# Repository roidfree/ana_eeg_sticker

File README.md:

# ANA - EEG Focus Monitor

A Flutter app that connects to state-of-the-art biosignal patch via Bluetooth to monitor focus, stress, and mental state in real-time.

## 🧠 What is ANA?

ANA is a wireless EEG monitoring system that turns brain activity into actionable insights. Think of it as a fitness tracker for your mind - it measures focus levels, stress, and mental fatigue to help you optimize your cognitive performance.

## 📱 Features

- **Real-time EEG monitoring** via Bluetooth Low Energy
- **Live focus tracking** with visual feedback
- **Stress level detection** using brain wave analysis
- **Session recording** and playback
- **Clean, intuitive interface** designed for daily use

## 🚀 Quick Start

### Prerequisites
- Flutter SDK (3.16+)
- Android Studio or Xcode
- Compatible EEG device (OpenBCI Cyton, nRF52832 prototype)

### Installation
```bash
# Clone the repository
git clone https://github.com/your-username/ana-app.git
cd ana_eeg_sticker

# Install dependencies
flutter pub get

# Run the app
flutter run
```

## 📦 Dependencies

```yaml
dependencies:
  flutter_blue_plus: ^1.12.0  # BLE connectivity
  fl_chart: ^0.65.0           # Real-time charts
  riverpod: ^2.4.0            # State management
  hive: ^2.2.3                # Local storage
```

## 🔧 Usage

1. **Connect Device**: Turn on your EEG device and tap "Scan" in the app
2. **Start Session**: Once connected, press "Start Monitoring" 
3. **View Live Data**: Watch your brain waves and focus metrics in real-time
4. **Review Sessions**: Check your focus patterns and improvements over time

## 📊 How It Works

```
EEG Sensor → Bluetooth → Signal Processing → Algorithms (e.g Focus) → Live Display
```

The app does things like: filter EEG signals (1-40 Hz), extracts alpha and beta wave features, and calculates a real-time focus score based on established neuroscience research.

## 🧪 Signal Processing

- **Bandpass filtering**: Removes noise and isolates brain waves
- **Feature extraction**: Alpha (8-12 Hz) and Beta (13-30 Hz) power
- **Focus metric**: Alpha/Beta ratio with smoothing algorithm
- **Real-time processing**: <100ms latency for immediate feedback

## 🛠️ Development

### Project Structure
```
lib/
├── main.dart              # App entry point
├── models/                # Data structures
├── services/              # BLE and signal processing
├── screens/               # UI screens
└── widgets/               # Reusable components
```

### Running Tests
```bash
flutter test
```

### Building for Release
```bash
# Android
flutter build apk --release

# iOS
flutter build ios --release
```

## 📱 Screenshots

[Add screenshots of your app here]

## 🎯 Roadmap

- [x] BLE connectivity
- [x] Real-time EEG display
- [x] Basic focus metrics
- [ ] Advanced signal processing
- [ ] Cloud data sync
- [ ] Multi-device support
- [ ] Meditation guidance

## 🤝 Contributing

We're a small team building this in the open. Feel free to:
- Report bugs via GitHub Issues
- Suggest features
- Submit pull requests

## 📄 License

MIT License - see [LICENSE](LICENSE) file for details.

## 🔗 Hardware Compatibility

**Tested Devices:**
- OpenBCI Cyton Board
- Custom nRF52832 prototype

**BLE Requirements:**
- Bluetooth 4.0+
- Custom EEG data characteristic
- Sampling rate: 250+ Hz

## 📧 Contact

For questions about the project or collaboration opportunities, create an issue or reach out via GitHub.

---

**Built with ❤️ for better brain health and cognitive performance.**

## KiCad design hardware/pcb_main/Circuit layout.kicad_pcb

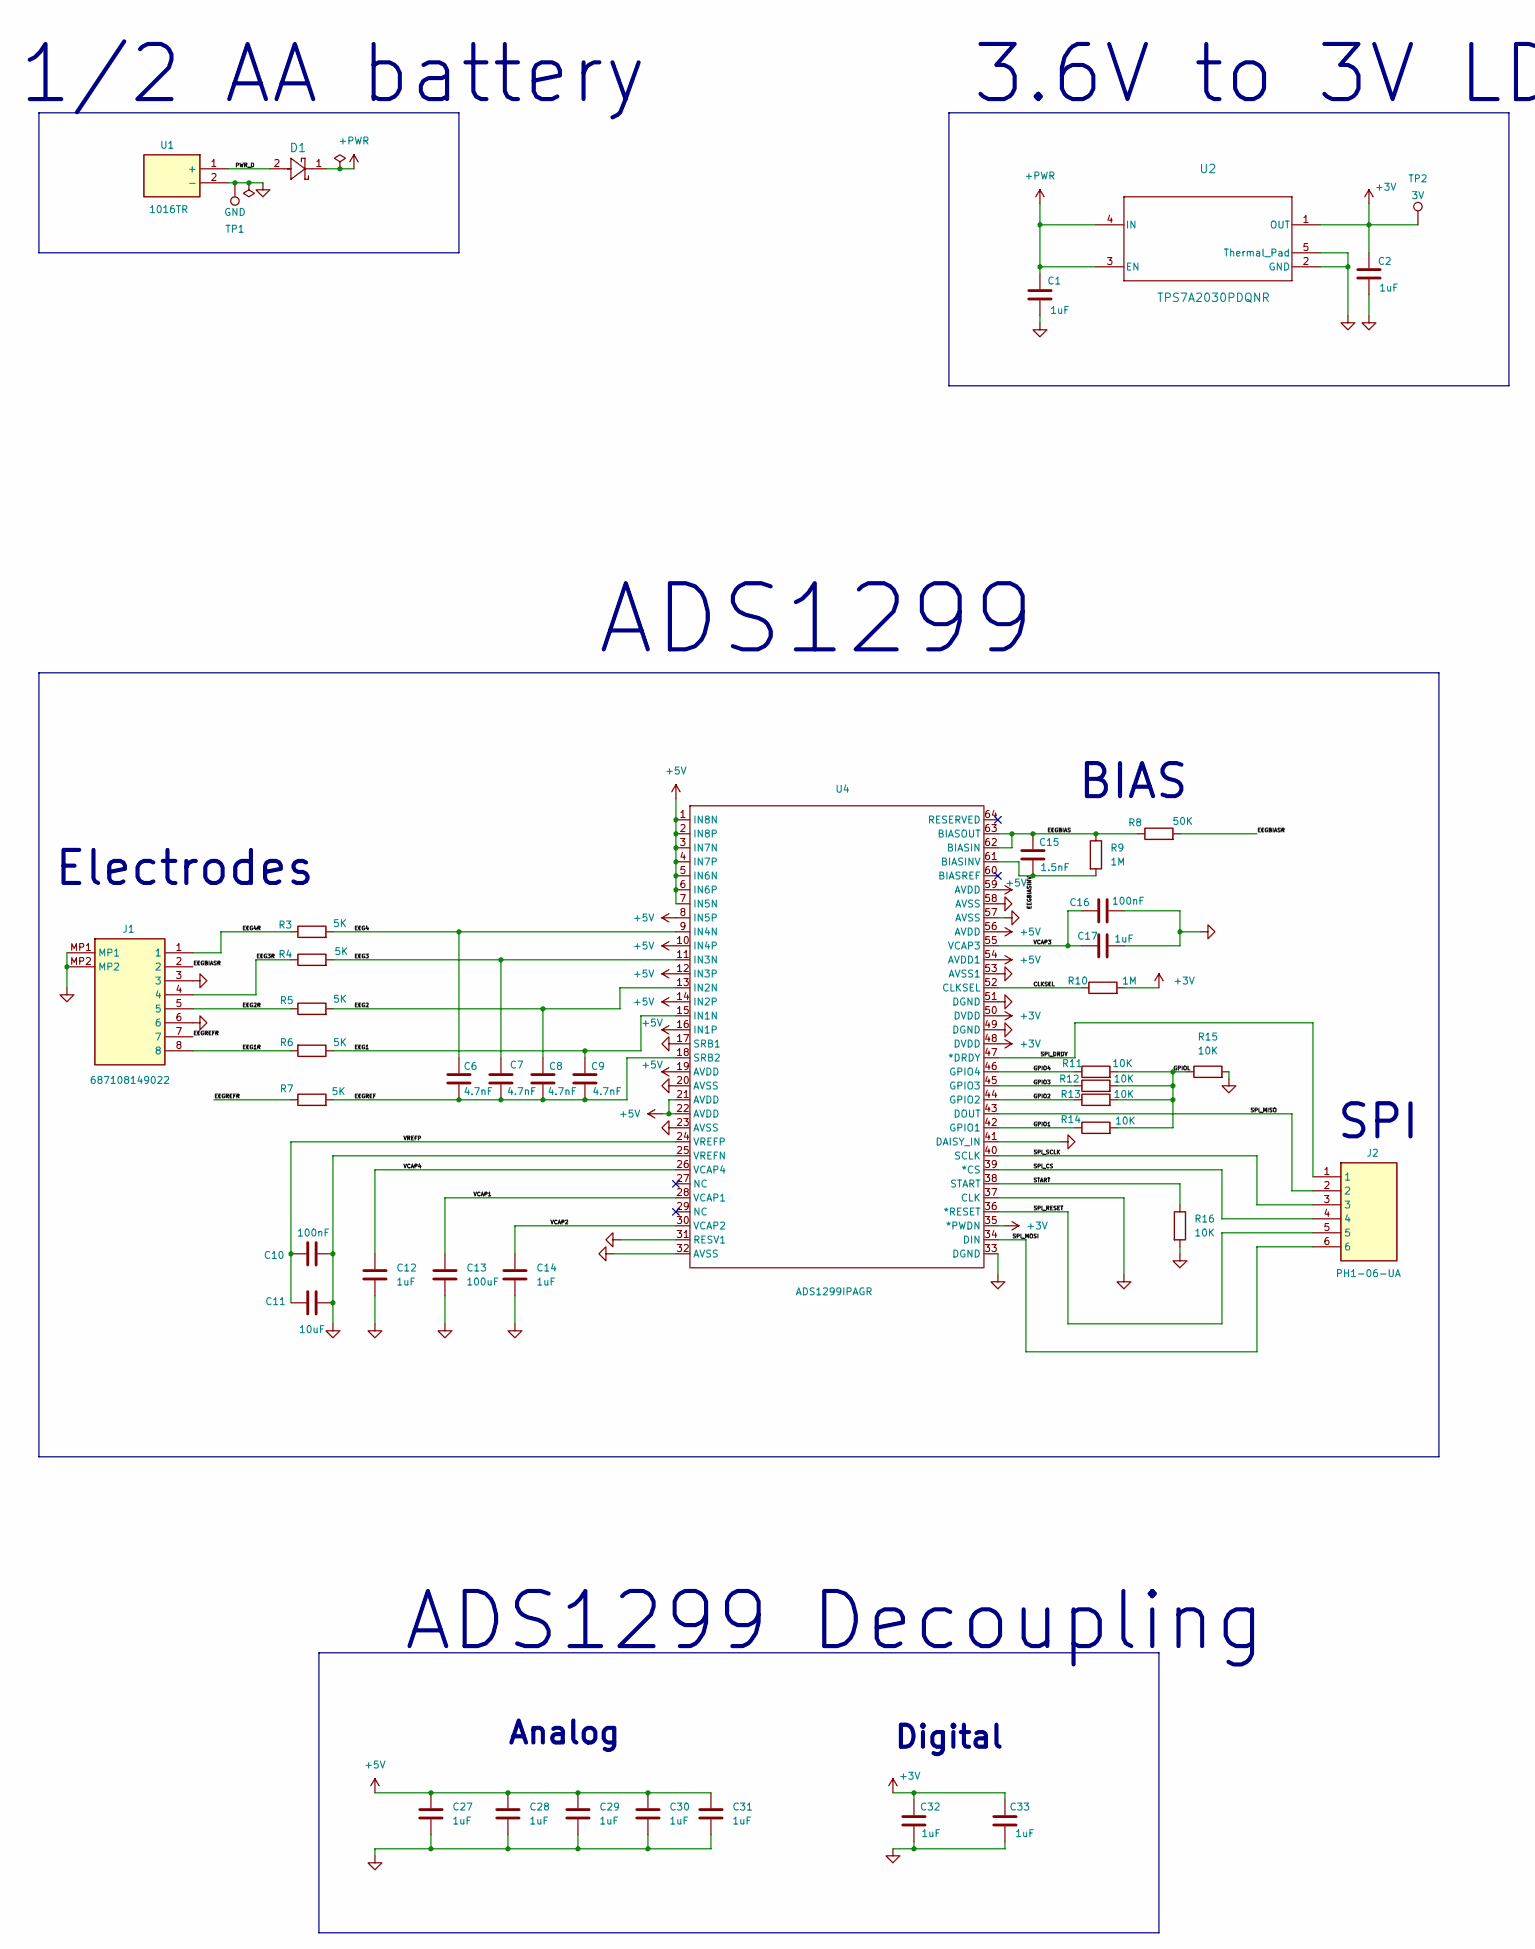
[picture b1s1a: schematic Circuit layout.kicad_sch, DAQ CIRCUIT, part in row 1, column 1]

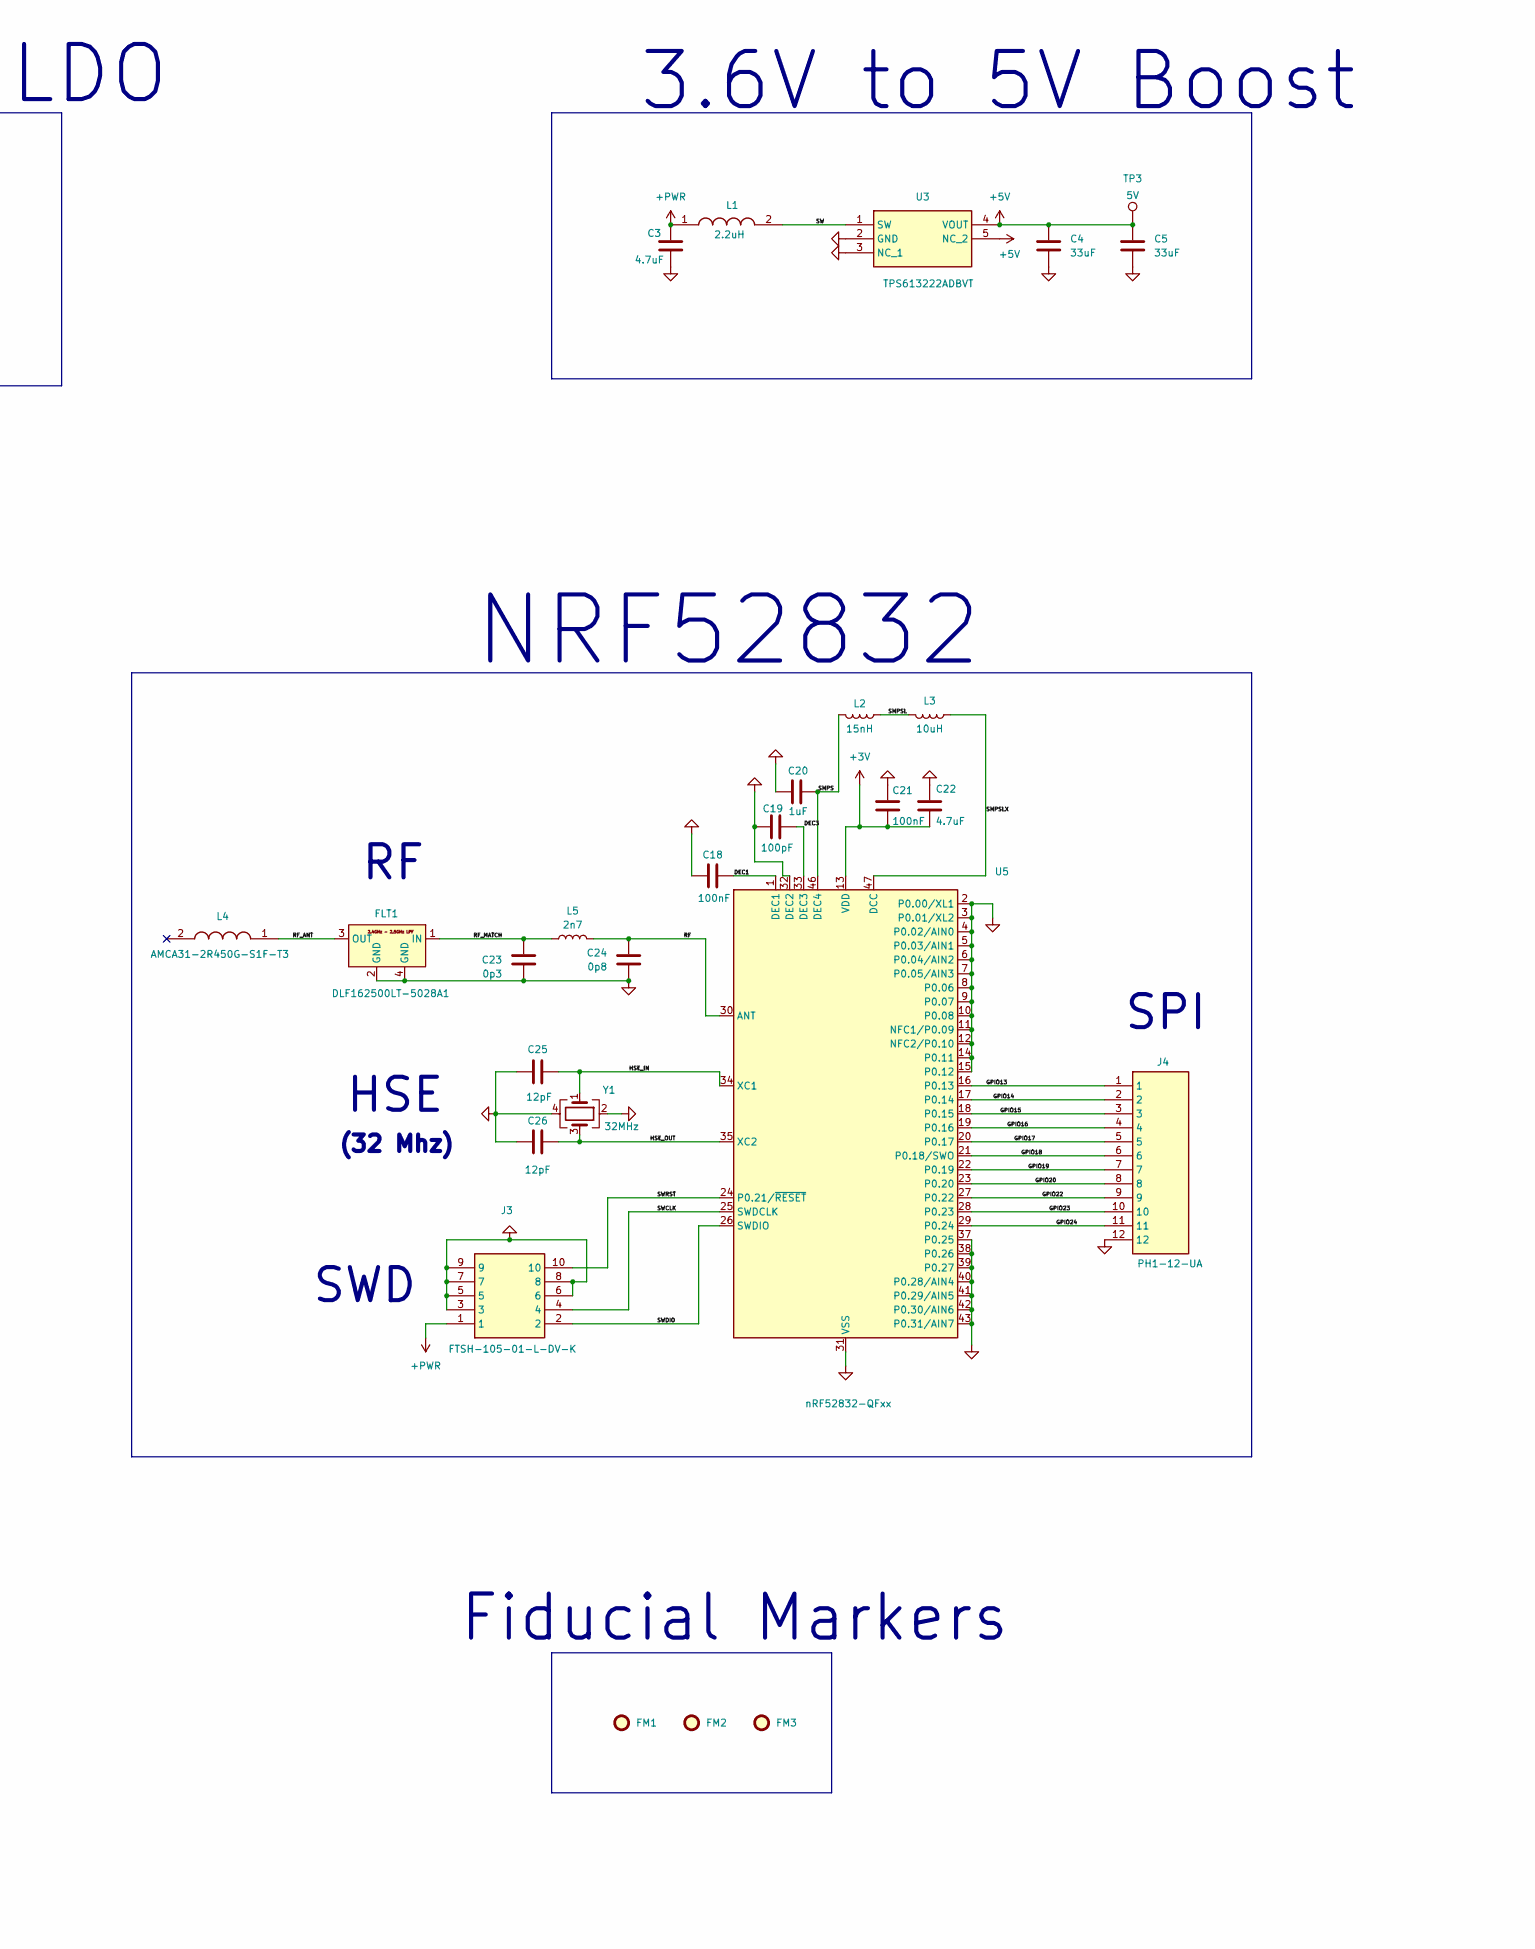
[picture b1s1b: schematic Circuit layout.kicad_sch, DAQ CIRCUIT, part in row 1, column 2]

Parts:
C1, C2, C12, C14, C17, C20, C27, C28, C29, C30, C31, C32, C33: 1uF; C_0402_1005Metric_Pad0.74x0.62mm_HandSolder; Manufacturer Part Number 04024D105KAT2A
C3, C22: 4.7uF; C_0402_1005Metric_Pad0.74x0.62mm_HandSolder; Manufacturer Part Number CM05X5R475M16AH
C4, C5: 33uF; C_0805_2012Metric; Manufacturer Part Number C2012X5R1A336M125AC
C6, C7, C8, C9: 4.7nF; C_0402_1005Metric_Pad0.74x0.62mm_HandSolder; Manufacturer Part Number GRM1555C1H472GE01D
C10, C16, C18, C21: 100nF; C_0402_1005Metric_Pad0.74x0.62mm_HandSolder; Manufacturer Part Number 04026C104MAT2A
C11: 10uF; C_0402_1005Metric_Pad0.74x0.62mm_HandSolder; Manufacturer Part Number C0402C106M7PAC7867
C13: 100uF; C_0805_2012Metric_Pad1.18x1.45mm_HandSolder; Manufacturer Part Number GRM21BR60G107ME11K
C15: 1.5nF; C_0402_1005Metric_Pad0.74x0.62mm_HandSolder; Manufacturer Part Number 04026C152KAT2A
C19: 100pF; C_0402_1005Metric_Pad0.74x0.62mm_HandSolder; Manufacturer Part Number 04026C101KAT2A
C23: 0p3; C_0402_1005Metric; Manufacturer Part Number GRM1555C1HR30WA01D
C24: 0p8; C_0402_1005Metric; Manufacturer Part Number GJM1555C1HR80BB01J
C25, C26: 12pF; C_0603_1608Metric_Pad1.08x0.95mm_HandSolder; Manufacturer Part Number C0603C120K9RAC7411
D1: CDBU0130L; Manufacturer Part Number CDBU0130L
FLT1: DLF162500LT-5028A1; Manufacturer Part Number DLF162500LT-5028A1
FM1, FM2, FM3: Fiducial; Fiducial_1mm_Mask2mm
J1: 687108149022; Mouser Part Number 710-687108149022
J2: PH1-06-UA; Mouser Part Number 737-PH1-06-UA
J3: FTSH-105-01-L-DV-K; FTSH10501LDVK; Mouser Part Number 200-FTSH10501LDVK
J4: PH1-12-UA; Mouser Part Number 737-PH1-12-UA
L1: 2.2uH; DFE252012F-2R2M=P2; Mouser Part Number 81-DFE252012F-2R2MP2
L2: 15nH; L_0402_1005Metric_Pad0.77x0.64mm_HandSolder; Manufacturer Part Number LQW15AN15NG8ZD
L3: 10uH; L_1008_2520Metric_Pad1.43x2.20mm_HandSolder; Manufacturer Part Number S1008R-103J
L4: AMCA31-2R450G-S1F-T3; Manufacturer Part Number AMCA31-2R450G-S1F-T3
L5: 2n7; L_0402_1005Metric; Manufacturer Part Number LQG15HS2N7S02D
R3, R4, R5, R6, R7: 5K; R_0402_1005Metric_Pad0.72x0.64mm_HandSolder; Manufacturer Part Number RC0402FR-075KL
R8: 50K; R_0402_1005Metric_Pad0.72x0.64mm_HandSolder; Manufacturer Part Number CRCW040250K0FKED
R9, R10: 1M; R_0402_1005Metric_Pad0.72x0.64mm_HandSolder; Manufacturer Part Number CRCW04021M00JNTD
R11, R12, R13, R14, R15, R16: 10K; R_0402_1005Metric_Pad0.72x0.64mm_HandSolder; Manufacturer Part Number 560112110006
TP1: GND; TestPoint_Pad_D2.0mm
TP2: 3V; TestPoint_Pad_D2.0mm
TP3: 5V; TestPoint_Pad_D2.0mm
U1: 1016TR; Mouser Part Number 534-1016TR
U2: TPS7A2030PDQNR; Manufacturer Part Number TPS7A2030PDQNR
U3: TPS613222ADBVT; Mouser Part Number 595-TPS613222ADBVT
U4: ADS1299IPAGR; Manufacturer Part Number ADS1299IPAGR
U5: nRF52832-QFxx; NRF52832-QFAA-R; Manufacturer Part Number nRF52832-QFAA-R
Y1: 32MHz; Crystal_SMD_3225-4Pin_3.2x2.5mm_HandSoldering; Manufacturer Part Number CX3225CA32000D0HSSCC

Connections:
+3V: C2.1, C21.1, C22.2, C32.1, C33.1, R10.2, TP2.1, U2.1 (OUT), U4.35 (*PWDN), U4.48 (DVDD), U4.50 (DVDD), U5.13 (VDD), U5.36 (VDD), U5.48 (VDD)
+5V: C4.1, C5.1, C27.1, C28.1, C29.1, C30.1, C31.1, TP3.1, U3.4 (VOUT), U3.5 (NC_2), U4.1 (IN8N), U4.2 (IN8P), U4.3 (IN7N), U4.4 (IN7P), U4.5 (IN6N), U4.6 (IN6P), U4.7 (IN5N), U4.8 (IN5P), U4.10 (IN4P), U4.12 (IN3P), U4.14 (IN2P), U4.16 (IN1P), U4.19 (AVDD), U4.21 (AVDD), U4.22 (AVDD), U4.54 (AVDD1), U4.56 (AVDD), U4.59 (AVDD)
+PWR: C1.1, C3.1, D1.1, J3.1, L1.1, U2.3 (EN), U2.4 (IN)
/CLKSEL: R10.1, U4.52 (CLKSEL)
/DEC1: C18.1, U5.1 (DEC1)
/DEC3: C19.2, U5.33 (DEC3)
/EEG1: C9.2, R6.1, U4.15 (IN1N)
/EEG1R: J1.8, R6.2
/EEG2: C8.1, R5.2, U4.13 (IN2N)
/EEG2R: J1.5, R5.1
/EEG3: C7.1, R4.2, U4.11 (IN3N)
/EEG3R: J1.4, R4.1
/EEG4: C6.1, R3.2, U4.9 (IN4N)
/EEG4R: J1.1, R3.1
/EEGBIAS: C15.2, R8.1, R9.1, U4.62 (BIASIN), U4.63 (BIASOUT)
/EEGBIASINV: C15.1, R9.2, U4.61 (BIASINV)
/EEGBIASR: J1.2, R8.2
/EEGREF: C6.2, C7.2, C8.2, C9.1, R7.2, U4.18 (SRB2)
/EEGREFR: J1.7, R7.1
/GPIO1: R14.1, U4.42 (GPIO1)
/GPIO2: R13.1, U4.44 (GPIO2)
/GPIO3: R12.1, U4.45 (GPIO3)
/GPIO4: R11.1, U4.46 (GPIO4)
/GPIO13: J4.1, U5.16 (P0.13)
/GPIO14: J4.2, U5.17 (P0.14)
/GPIO15: J4.3, U5.18 (P0.15)
/GPIO16: J4.4, U5.19 (P0.16)
/GPIO17: J4.5, U5.20 (P0.17)
/GPIO18: J4.6, U5.21 (P0.18/SWO)
/GPIO19: J4.7, U5.22 (P0.19)
/GPIO20: J4.8, U5.23 (P0.20)
/GPIO22: J4.9, U5.27 (P0.22)
/GPIO23: J4.10, U5.28 (P0.23)
/GPIO24: J4.11, U5.29 (P0.24)
/GPIOL: R11.2, R12.2, R13.2, R14.2, R15.1
/HSE_IN: C25.1, U5.34 (XC1), Y1.1
/HSE_OUT: C26.1, U5.35 (XC2), Y1.3
/PWR_D: D1.2, U1.1 (+)
/RF: C24.1, L5.1, U5.30 (ANT)
/RF_ANT: FLT1.3 (OUT), L4.1 (FEED)
/RF_MATCH: C23.1, FLT1.1 (IN), L5.2
/SMPS: C20.1, L2.2, U5.46 (DEC4)
/SMPSL: L2.1, L3.2
/SMPSLX: L3.1, U5.47 (DCC)
/SPI_CS: J2.4, U4.39 (*CS)
/SPI_DRDY: J2.1, U4.47 (*DRDY)
/SPI_MISO: J2.2, U4.43 (DOUT)
/SPI_MOSI: J2.6, U4.34 (DIN)
/SPI_RESET: J2.5, U4.36 (*RESET)
/SPI_SCLK: J2.3, U4.40 (SCLK)
/START: R16.1, U4.38 (START)
/SW: L1.2, U3.1 (SW)
/SWCLK: J3.4, U5.25 (SWDCLK)
/SWDIO: J3.2, U5.26 (SWDIO)
/SWRST: J3.10, U5.24 (P0.21/~RESET)
/VCAP1: C13.1, U4.28 (VCAP1)
/VCAP2: C14.1, U4.30 (VCAP2)
/VCAP3: C16.2, C17.1, U4.55 (VCAP3)
/VCAP4: C12.1, U4.26 (VCAP4)
/VREFP: C10.1, C11.2, U4.24 (VREFP)
GND: C1.2, C2.2, C3.2, C4.2, C5.2, C10.2, C11.1, C12.2, C13.2, C14.2, C16.1, C17.2, C18.2, C19.1, C20.2, C21.2, C22.1, C23.2, C24.2, C25.2, C26.2, C27.2, C28.2, C29.2, C30.2, C31.2, C32.2, C33.2, FLT1.2 (GND), FLT1.4 (GND), J1.3, J1.6, J1.MP1, J1.MP2, J3.3, J3.5, J3.6, J3.7, J3.8, J3.9, J4.12, R15.2, R16.2, TP1.1, U1.2 (-), U2.2 (GND), U2.5 (Thermal_Pad), U3.2 (GND), U3.3 (NC_1), U4.17 (SRB1), U4.20 (AVSS), U4.23 (AVSS), U4.25 (VREFN), U4.31 (RESV1), U4.32 (AVSS), U4.33 (DGND), U4.37 (CLK), U4.41 (DAISY_IN), U4.49 (DGND), U4.51 (DGND), U4.53 (AVSS1), U4.57 (AVSS), U4.58 (AVSS), U5.2 (P0.00/XL1), U5.3 (P0.01/XL2), U5.4 (P0.02/AIN0), U5.5 (P0.03/AIN1), U5.6 (P0.04/AIN2), U5.7 (P0.05/AIN3), U5.8 (P0.06), U5.9 (P0.07), U5.10 (P0.08), U5.11 (NFC1/P0.09), U5.12 (NFC2/P0.10), U5.14 (P0.11), U5.15 (P0.12), U5.31 (VSS), U5.32 (DEC2), U5.37 (P0.25), U5.38 (P0.26), U5.39 (P0.27), U5.40 (P0.28/AIN4), U5.41 (P0.29/AIN5), U5.42 (P0.30/AIN6), U5.43 (P0.31/AIN7), U5.45 (VSS), U5.49 (VSS), Y1.2, Y1.4

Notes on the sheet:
Electrodes
1/2 AA battery
Digital
3.6V to 5V Boost
SWD
ADS1299
SPI
HSE
NRF52832
(32 Mhz)
Analog
ADS1299 Decoupling
BIAS
Fiducial Markers
3.6V to 3V LDO

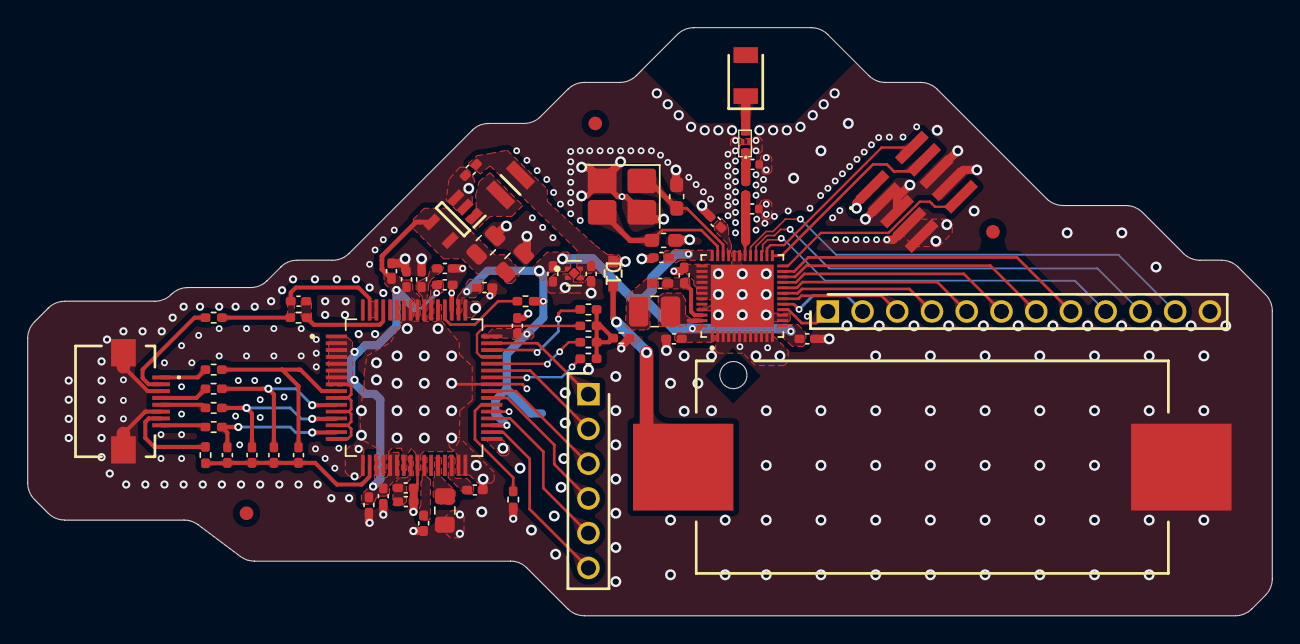
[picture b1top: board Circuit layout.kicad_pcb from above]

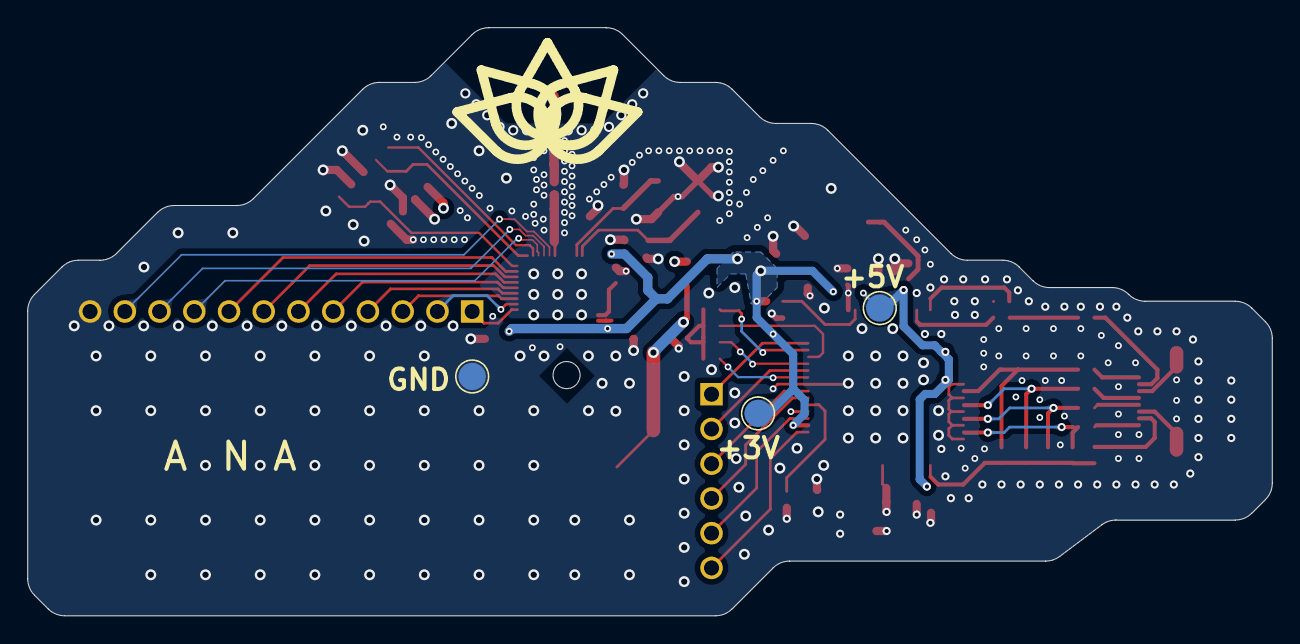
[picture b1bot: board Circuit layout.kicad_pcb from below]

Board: 4 copper layers, 91.0 x 43.0 mm, 70 parts (3 on the bottom side), 61 nets.

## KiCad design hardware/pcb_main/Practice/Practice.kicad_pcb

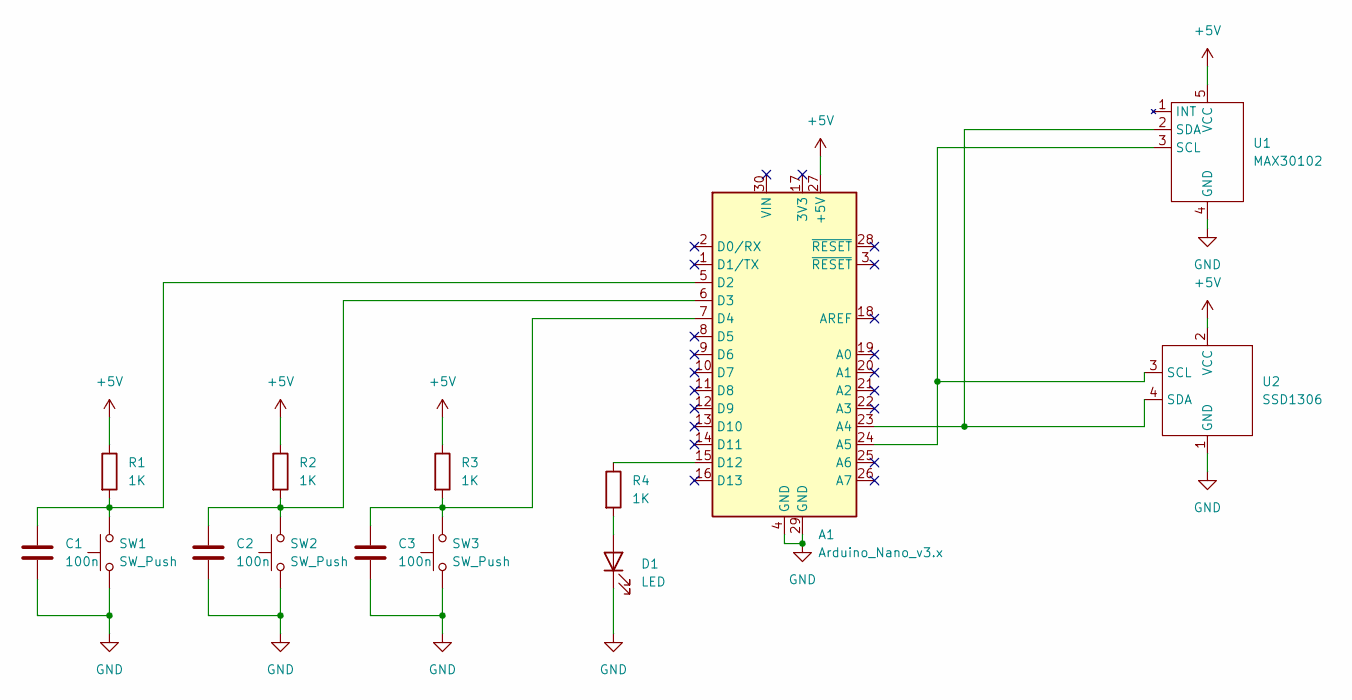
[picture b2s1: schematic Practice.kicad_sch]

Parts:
A1: Arduino_Nano_v3.x; Arduino_Nano
C1, C2, C3: 100n; C_Disc_D4.7mm_W2.5mm_P5.00mm
D1: LED; LED_D5.0mm
R1, R2, R3, R4: 1K; R_Axial_DIN0207_L6.3mm_D2.5mm_P7.62mm_Horizontal
SW1, SW2, SW3: SW_Push; SW_PUSH_6mm
U1: MAX30102
U2: SSD1306

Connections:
+5V: A1.27 (+5V), R1.1, R2.1, R3.1, U1.5 (VCC), U2.2 (VCC)
GND: A1.4 (GND), A1.29 (GND), C1.2, C2.2, C3.2, D1.1 (K), SW1.1, SW2.1, SW3.1, U1.4 (GND), U2.1 (GND)
unnamed: A1.23 (A4), U1.2 (SDA), U2.4 (SDA)
unnamed: A1.24 (A5), U1.3 (SCL), U2.3 (SCL)
unnamed: A1.5 (D2), C1.1, R1.2, SW1.2
unnamed: A1.6 (D3), C2.1, R2.2, SW2.2
unnamed: A1.7 (D4), C3.1, R3.2, SW3.2
unnamed: A1.15 (D12), R4.1
unnamed: D1.2 (A), R4.2

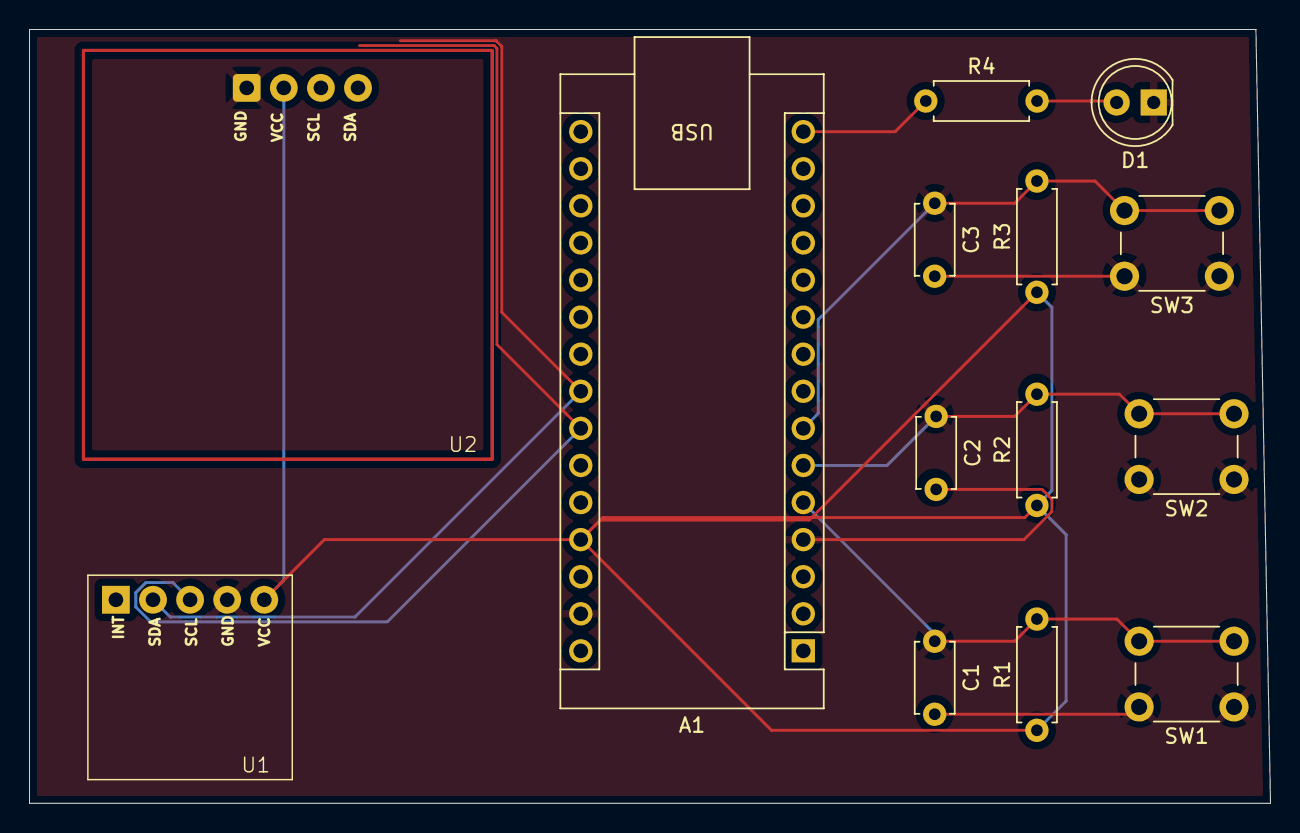
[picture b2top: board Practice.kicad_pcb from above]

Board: 4 copper layers, 85.0 x 53.0 mm, 14 parts (0 on the bottom side), 9 nets.

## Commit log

2025-02-22 only code should go on here mb
2025-06-30 Project scaffolded
2025-06-30 updating name and logo
2025-06-30 logo update
2025-06-30 finalised logo
2025-06-30 moved around file structure
    Python will handle backend signal processing and potentially ML pipeline, needs internet though
2025-06-30 deleting old android on keerans end
2025-06-30 test: ios folder removed
2025-06-30 change home screen title
2025-07-02 fix: gitignore fixed
    Was trying to sync files for many files and folders that were unncessary. Need to also ignore the nested folders in build
2025-07-02 Added homescreen
    Finally reinstated changed
2025-07-05 adding home page with swiping messages
2025-07-07 minor file structure changes for hardware
    Inclusion of hardware logging of project inthis monorepo
2025-07-07 Kicad schematics added of the main circuit, missing connector and EOG not removed
2025-07-07 changed fonts and added continuous nav bar
    bottom nav bar always present - created buttons and new screens for all buttons present on the home screen
2025-07-07 fixing main dart screen
2025-07-07 fix: commented flutter_blue package for now
2025-07-09 first bluetooth connection attempt
    Backend architecture chosen: Cyton board -> Flutter BLE (with connection screen Connect to Device) -> send off data after session via internet to Python backend server for analysis, then results are 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
2025-07-09 added start session animation and scrolling functionality to home screen
2025-07-09 added bluetooth functionality to the start session button
2025-07-14 Added footprints - Dillon
    Added footprints, symbols and 3d models
    Now need to update with new antenna
2025-07-15 test points added
    also, antenna added, component numbering done, all footprints there, need to populate BOM
2025-07-16 Tidied up
    Boxes, capacitor replamcents,
2025-07-19 Schematic + BOM finished
2025-07-23 spi_loopback
2025-07-23 Added lots
    Started bridge pcb
    Added pin header for cyton
    Now only using 4 electrodes
    Add header for SWD interface
2025-07-24 improving graphs on alanlytics page
2025-07-26 Battery, zif added
    nrf test points reduced
2025-08-01 added more dependencies
2025-08-03 Bridges done, main layout done
    layer pours done
    CHanged zif connector to 8 wide to the bridge
    Changed voltage levels
2025-08-03 changing components
2025-08-04 fake eeg ble added
2025-08-04 ble sim
2025-08-04 ble sim added
2025-08-04 small fix to my git
2025-08-04 small fix for my git again
2025-08-11 both bridge finished
    main pcb layout nearly there
2025-08-12 cannow stream data from practice ble device
2025-08-13 first attempt at updating every minute to classify focus and stress using dart (no python)
2025-08-13 layout finalised, routing started
    more board fills, electrode routing done, faraday cage around electrode traces
2025-08-19 Most of routing done
    need to do power routing and add reverse voltage protection
2025-08-20 Most of routing done
    Just GNDing left
2025-08-29 STREAMS DATA WELL, ANALYTICS UI CHANGED, TIMEFRAME ZOOM FUNCTIONALITY AND CLEAR DATA FUNCTINALITY ADDED. STILL A BUG WITH ZOOMING, SOME MNUTES ARENT INCLUDED
2025-08-29 zooming works much better now can stream well
2025-08-30 All done, main and bridge 4 done
    final push for a while
2025-09-18 Final push for now
    All bridges ordered, main DAQ ordered,
    Main DAQ needed 1 tweak to prevent short circuit due to close by traces
2025-09-18 Firmware README.md
2025-09-18 cleaned up github, added and removed final versions of files
